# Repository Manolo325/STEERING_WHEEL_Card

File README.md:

# Volant
Mettre à jour la carte volant du TIM

# Fonctions à accomplir

- Programable de l'exterieur
- Affichage à l'écran de : 
	- La vitesse 
	- (Temoins freinage)
	- (Temoins feu avant /arrire)
	- (Temoins direction)

- Saisie de :
	- la vitesse limite
	- Phare avant / arriere
	- Feux de direction
	- Feu de freinage
	- Essuie glace 
	- marche avant/ marche arriere
	- acceleration
	- consigne de courant
	- POWER ON/OFF (potentiel)

- Communication CAN avec :
	- Lumiere avant/arriere
	- Feu de direction
	- Freinage (lumiere arriere)
	 ATTENTION : Cable signalant le freinage doit passer à coté du BUS CAN 
	- Vitesse 
	- Commande Moteur : Avant/Arriere/Courant

- ~~led temoins de :~~
	- ~~freinage~~
	- ~~feu de direction~~
	- ~~feu avant et arrire~~

# Materielle

- Affichache  :
	- (SPI) ecran e-paper hacked (refresh speed)
	- (SPI) ecran oled (potentiel ? )
- Saisie 
	- rotary encoder --> vitesse limite 
	- Potentiometre  --> selection consigne de courant 
	- lever switch   --> marche avant/arriere
	- push buttons   --> tous les autres

# limite mecanique (à chercher)

- le plus petit possible

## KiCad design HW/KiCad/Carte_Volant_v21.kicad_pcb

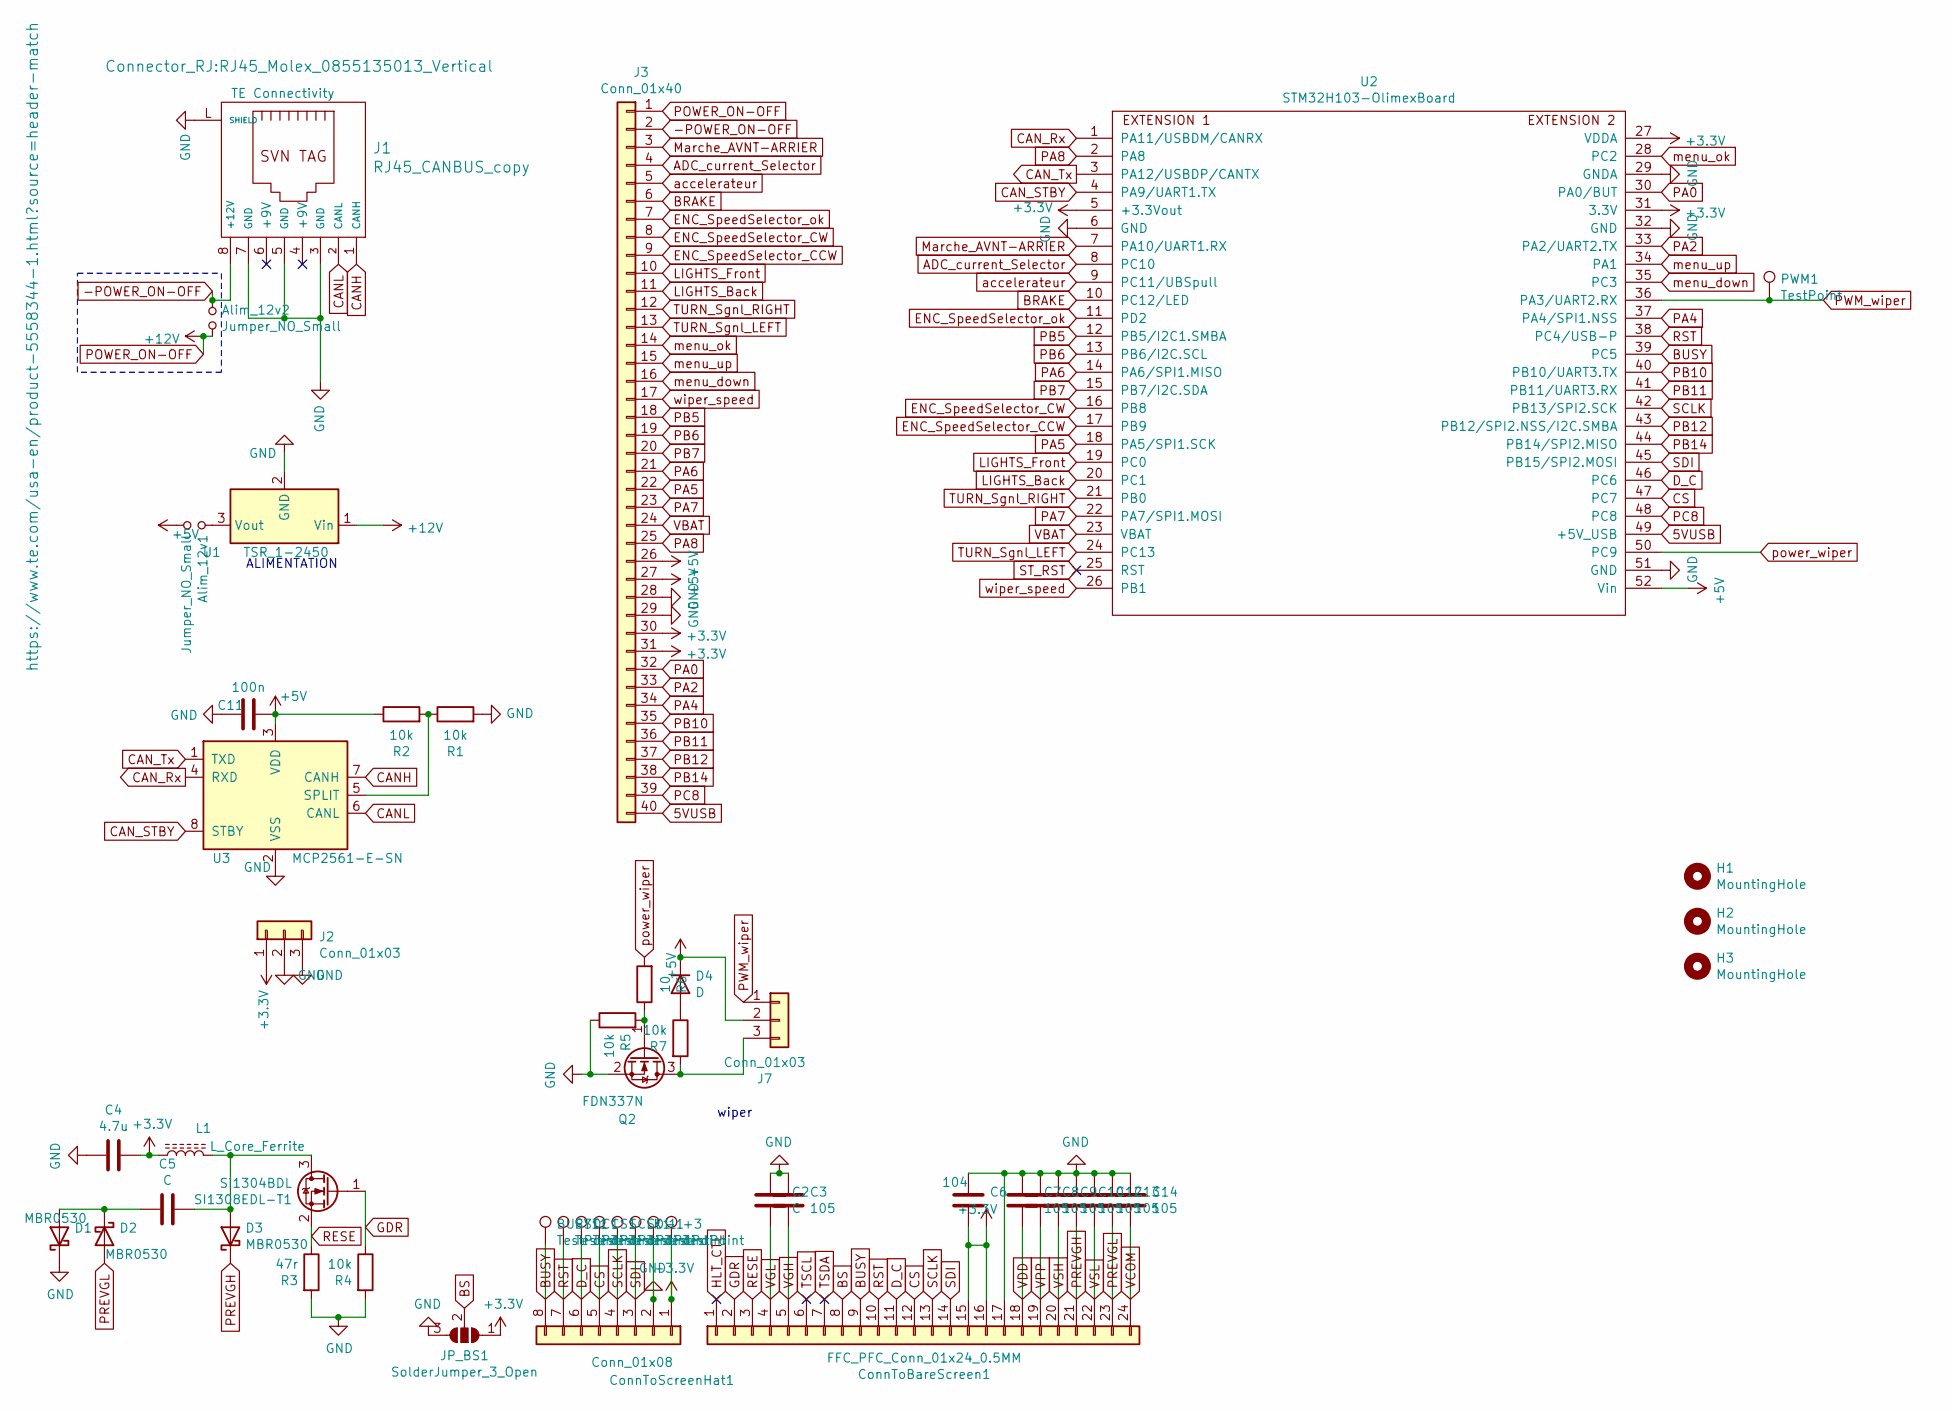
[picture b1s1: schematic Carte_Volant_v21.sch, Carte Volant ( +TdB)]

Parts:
+3: TestPoint; TestPoint_Pad_1.5x1.5mm
-1: TestPoint; TestPoint_Pad_1.5x1.5mm
Alim_12v1, Alim_12v2: Jumper_NO_Small; SolderJumper-2_P1.3mm_Open_Pad1.0x1.5mm
BUSY1: TestPoint; TestPoint_Pad_1.5x1.5mm
C2, C5: C; C_0603_1608Metric_Pad1.05x0.95mm_HandSolder
C3, C7, C8, C9, C10, C12, C13, C14: 105; C_0603_1608Metric_Pad1.05x0.95mm_HandSolder
C4: 4.7u; C_0603_1608Metric_Pad1.05x0.95mm_HandSolder
C6: 104; C_0603_1608Metric_Pad1.05x0.95mm_HandSolder
C11: 100n; C_0603_1608Metric_Pad1.05x0.95mm_HandSolder
CS1: TestPoint; TestPoint_Pad_1.5x1.5mm
ConnToBareScreen1: FFC_PFC_Conn_01x24_0.5MM; Hirose_FH12-24S-0.5SH_1x24-1MP_P0.50mm_Horizontal
ConnToScreenHat1: Conn_01x08; Molex_PicoBlade_53261-0871_1x08-1MP_P1.25mm_Horizontal
D1, D2, D3: MBR0530; D_SOD-123
D4: D; D_1206_3216Metric
DC1: TestPoint; TestPoint_Pad_1.5x1.5mm
H1, H2, H3: MountingHole; MountingHole_3.5mm
J1: RJ45_CANBUS_copy; RJ45_Molex_0855135013_Vertical; MPN 5558344-1
J2, J7: Conn_01x03; Molex_Micro-Fit_3.0_43650-0300_1x03_P3.00mm_Horizontal
J3: Conn_01x40; IDC-Header_2x20_P2.54mm_Vertical
JP_BS1: SolderJumper_3_Open; SolderJumper-3_P1.3mm_Open_Pad1.0x1.5mm
L1: L_Core_Ferrite; L_1206_3216Metric
PWM1: TestPoint; TestPoint_Pad_1.5x1.5mm
Q2: FDN337N; SOT-23
R1, R2, R4, R5, R7: 10k; R_0603_1608Metric_Pad1.05x0.95mm_HandSolder
R3: 47r; R_0603_1608Metric_Pad1.05x0.95mm_HandSolder
R6: 10; R_0603_1608Metric_Pad1.05x0.95mm_HandSolder
RST1: TestPoint; TestPoint_Pad_1.5x1.5mm
SCLK1: TestPoint; TestPoint_Pad_1.5x1.5mm
SDI1: TestPoint; TestPoint_Pad_1.5x1.5mm
SI1308EDL-T1: Si1304BDL; SOT-323_SC-70
U1: TSR_1-2450; Converter_DCDC_TRACO_TSR-1_THT
U2: STM32H103-OlimexBoard; STM32H103-Olimex_SMD
U3: MCP2561-E-SN; SOIC-8_3.9x4.9mm_P1.27mm

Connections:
5VUSB: J3.40, U2.49 (+5V_USB)
+3V3: +3.1, C4.1, C6.2, ConnToBareScreen1.15, ConnToBareScreen1.16, ConnToScreenHat1.1, J2.1, J3.30, J3.31, JP_BS1.1 (A), L1.1, U2.5 (+3.3Vout), U2.27 (VDDA), U2.31 (3.3V)
+5V: Alim_12v1.2, C11.2, D4.1 (K), J3.26, J3.27, J7.2, R2.1, U2.52 (Vin), U3.3 (VDD)
-POWER_ON-OFF: Alim_12v2.1, J1.8 (+12V), J3.2
ADC_current_Selector: J3.4, U2.8 (PC10)
BRAKE: J3.6, U2.10 (PC12/LED)
BS: ConnToBareScreen1.8, JP_BS1.2 (C)
BUSY: BUSY1.1, ConnToBareScreen1.9, ConnToScreenHat1.8, U2.39 (PC5)
CANH: J1.1 (CANH), U3.7 (CANH)
CANL: J1.2 (CANL), U3.6 (CANL)
CAN_Rx: U2.1 (PA11/USBDM/CANRX), U3.4 (RXD)
CAN_STBY: U2.4 (PA9/UART1.TX), U3.8 (STBY)
CAN_Tx: U2.3 (PA12/USBDP/CANTX), U3.1 (TXD)
CS: CS1.1, ConnToBareScreen1.12, ConnToScreenHat1.5, U2.47 (PC7)
D_C: ConnToBareScreen1.11, ConnToScreenHat1.6, DC1.1, U2.46 (PC6)
ENC_SpeedSelector_CCW: J3.9, U2.17 (PB9)
ENC_SpeedSelector_CW: J3.8, U2.16 (PB8)
ENC_SpeedSelector_ok: J3.7, U2.11 (PD2)
GDR: ConnToBareScreen1.2, R4.1, SI1308EDL-T1.1 (G)
GND: -1.1, C2.1, C3.1, C4.2, C6.1, C7.1, C8.1, C9.1, C10.1, C11.1, C12.1, C13.1, C14.1, ConnToBareScreen1.17, ConnToBareScreen1.MP, ConnToScreenHat1.2, ConnToScreenHat1.MP, D1.1 (K), J1.3 (GND), J1.5 (GND), J1.7 (GND), J1.L (SHIELD), J2.2, J2.3, J3.28, J3.29, JP_BS1.3 (B), Q2.2 (S), R1.2, R3.2, R4.2, R5.1, U1.2 (GND), U2.6 (GND), U2.29 (GNDA), U2.32 (GND), U2.51 (GND), U3.2 (VSS)
HLT_CTL: ConnToBareScreen1.1
LIGHTS_Back: J3.11, U2.20 (PC1)
LIGHTS_Front: J3.10, U2.19 (PC0)
Marche_AVNT-ARRIER: J3.3, U2.7 (PA10/UART1.RX)
unnamed: Alim_12v1.1, U1.3 (Vout)
unnamed: C5.1, D3.2 (A), L1.2, SI1308EDL-T1.3 (D)
unnamed: C5.2, D1.2 (A), D2.1 (K)
unnamed: D4.2 (A), R7.1
unnamed: J7.3, Q2.3 (D), R7.2
unnamed: Q2.1 (G), R5.2, R6.1
unnamed: R1.1, R2.2, U3.5 (SPLIT)
PA0: J3.32, U2.30 (PA0/BUT)
PA2: J3.33, U2.33 (PA2/UART2.TX)
PA4: J3.34, U2.37 (PA4/SPI1.NSS)
PA5: J3.22, U2.18 (PA5/SPI1.SCK)
PA6: J3.21, U2.14 (PA6/SPI1.MISO)
PA7: J3.23, U2.22 (PA7/SPI1.MOSI)
PA8: J3.25, U2.2 (PA8)
PB5: J3.18, U2.12 (PB5/I2C1.SMBA)
PB6: J3.19, U2.13 (PB6/I2C.SCL)
PB7: J3.20, U2.15 (PB7/I2C.SDA)
PB10: J3.35, U2.40 (PB10/UART3.TX)
PB11: J3.36, U2.41 (PB11/UART3.RX)
PB12: J3.37, U2.43 (PB12/SPI2.NSS/I2C.SMBA)
PB14: J3.38, U2.44 (PB14/SPI2.MISO)
PC8: J3.39, U2.48 (PC8)
POWER_ON-OFF: Alim_12v2.2, J3.1, U1.1 (Vin)
PREVGH: C10.2, ConnToBareScreen1.21, D3.1 (K)
PREVGL: C13.2, ConnToBareScreen1.23, D2.2 (A)
PWM_wiper: J7.1, PWM1.1, U2.36 (PA3/UART2.RX)
RESE: ConnToBareScreen1.3, R3.1, SI1308EDL-T1.2 (S)
RST: ConnToBareScreen1.10, ConnToScreenHat1.7, RST1.1, U2.38 (PC4/USB-P)
SCLK: ConnToBareScreen1.13, ConnToScreenHat1.4, SCLK1.1, U2.42 (PB13/SPI2.SCK)
SDI: ConnToBareScreen1.14, ConnToScreenHat1.3, SDI1.1, U2.45 (PB15/SPI2.MOSI)
ST_RST: U2.25 (RST)
TSCL: ConnToBareScreen1.6
TSDA: ConnToBareScreen1.7
TURN_Sgnl_LEFT: J3.13, U2.24 (PC13)
TURN_Sgnl_RIGHT: J3.12, U2.21 (PB0)
VBAT: J3.24, U2.23 (VBAT)
VCOM: C14.2, ConnToBareScreen1.24
VDD: C7.2, ConnToBareScreen1.18
VGH: C3.2, ConnToBareScreen1.5
VGL: C2.2, ConnToBareScreen1.4
VPP: C8.2, ConnToBareScreen1.19
VSH: C9.2, ConnToBareScreen1.20
VSL: C12.2, ConnToBareScreen1.22
accelerateur: J3.5, U2.9 (PC11/UBSpull)
menu_down: J3.16, U2.35 (PC3)
menu_ok: J3.14, U2.28 (PC2)
menu_up: J3.15, U2.34 (PA1)
power_wiper: R6.2, U2.50 (PC9)
wiper_speed: J3.17, U2.26 (PB1)

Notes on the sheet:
wiper
ALIMENTATION

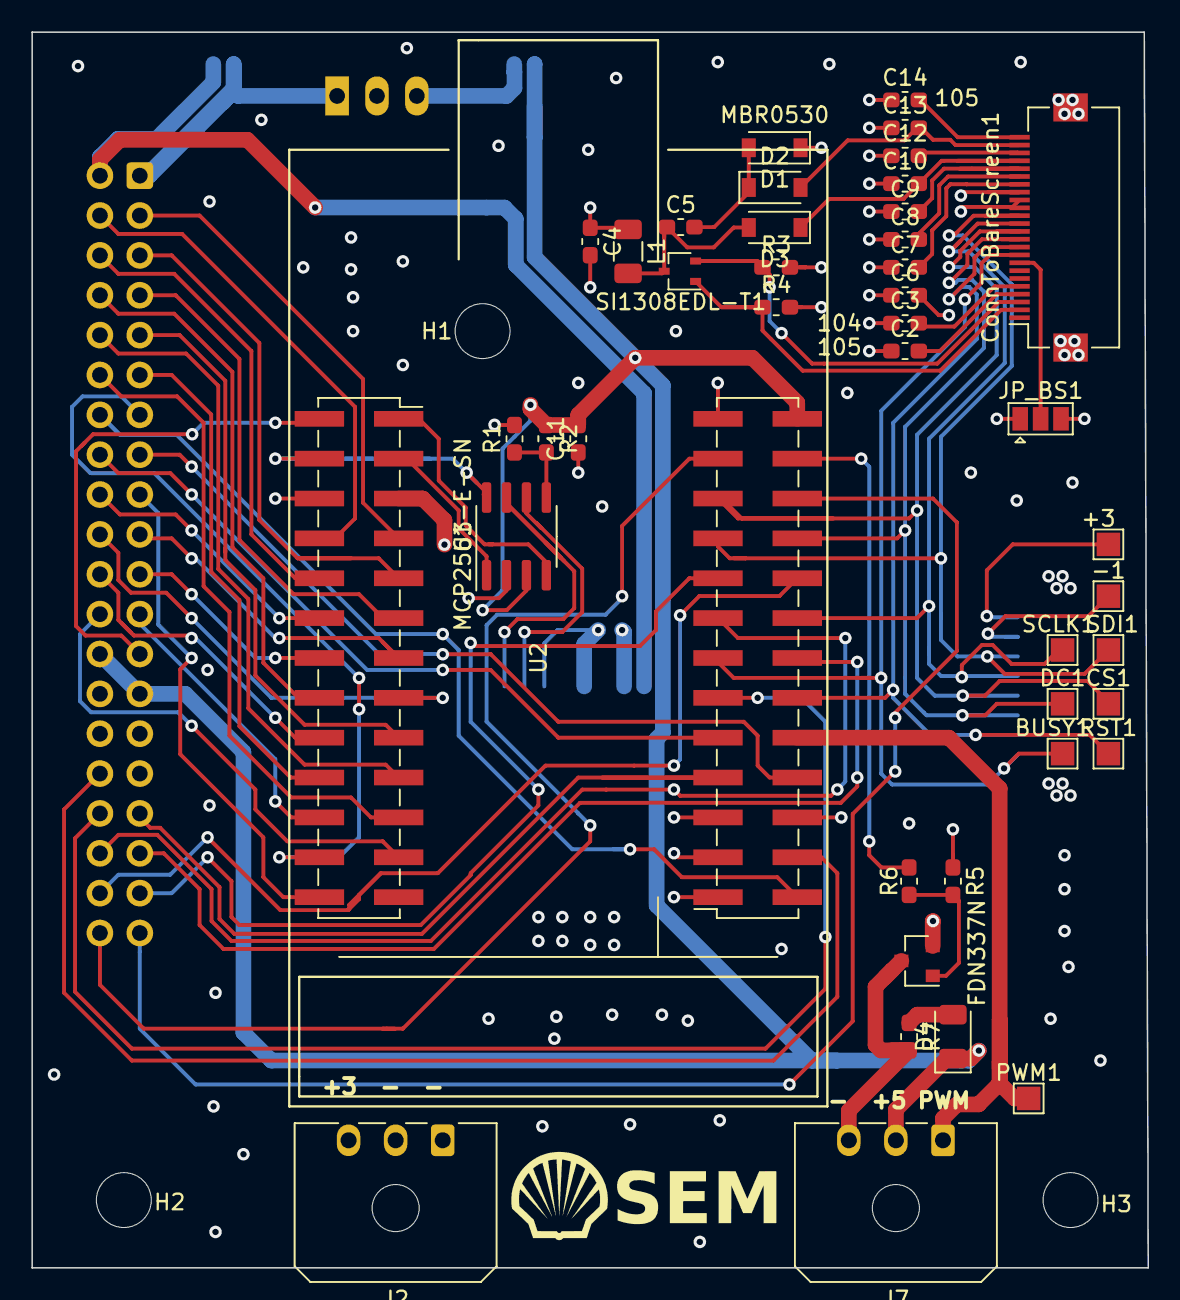
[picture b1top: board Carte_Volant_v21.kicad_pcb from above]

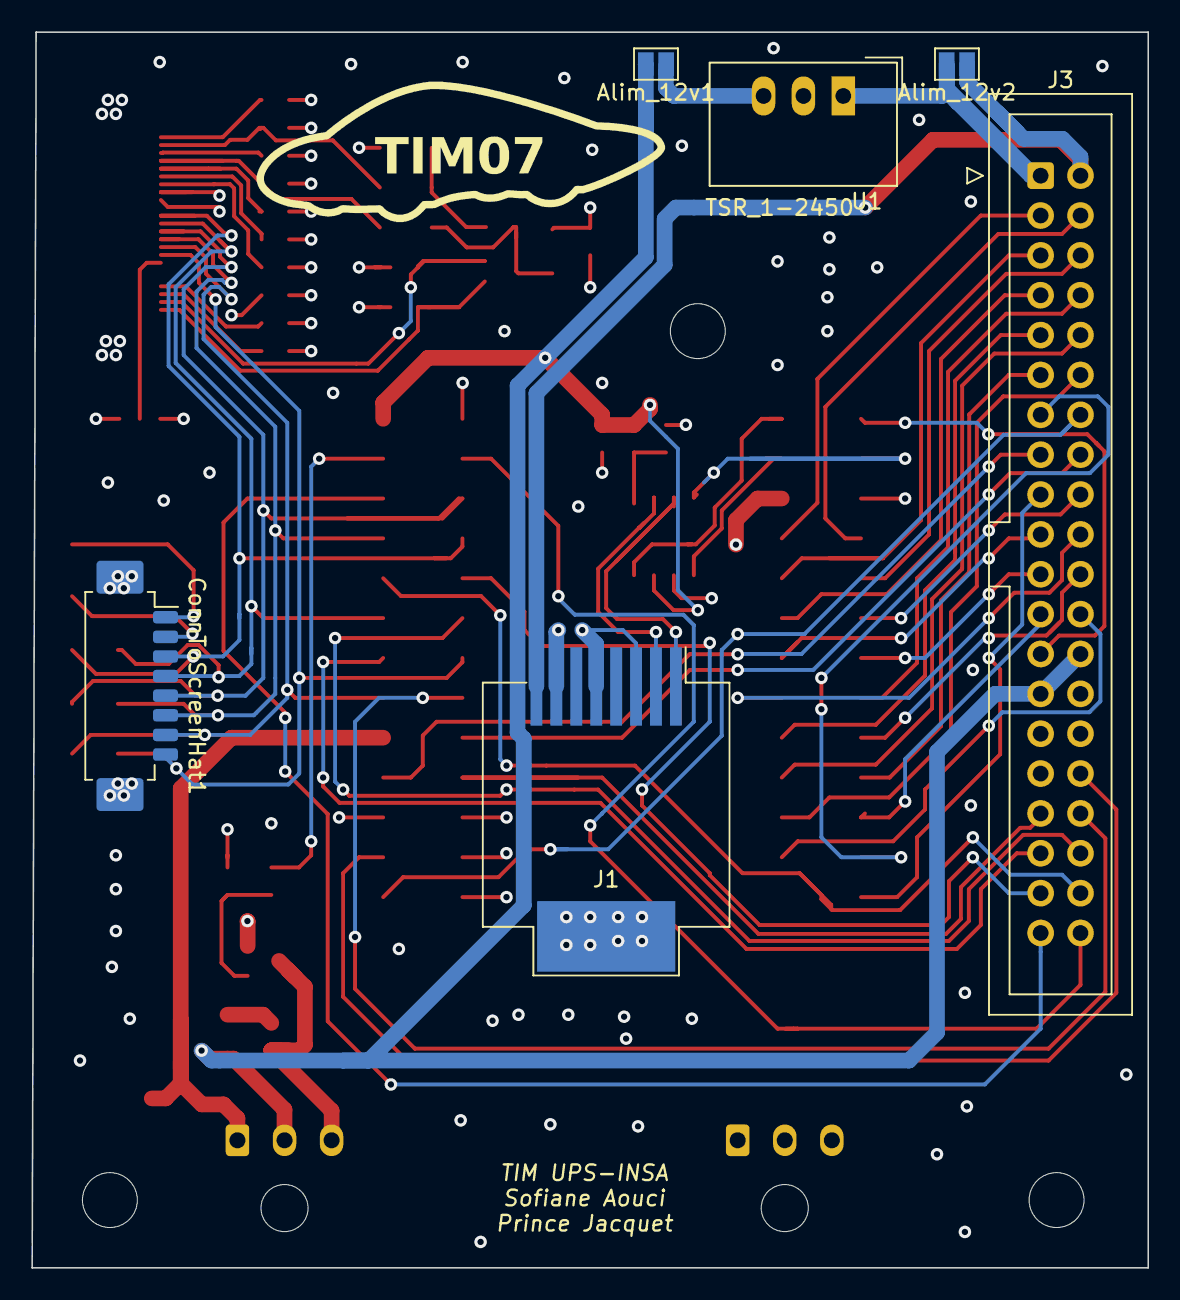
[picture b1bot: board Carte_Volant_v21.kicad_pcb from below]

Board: 4 copper layers, 71.1 x 78.7 mm, 53 parts (7 on the bottom side), 69 nets.

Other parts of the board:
VAL: REF; logo_tim07_medium_bottom
VAL#2: REF; logo_shell2_medium_top_silk

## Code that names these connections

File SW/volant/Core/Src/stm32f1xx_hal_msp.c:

/* USER CODE BEGIN Header */
/**
  ******************************************************************************
  * File Name          : stm32f1xx_hal_msp.c
  * Description        : This file provides code for the MSP Initialization
  *                      and de-Initialization codes.
  ******************************************************************************
  * @attention
  *
  * <h2><center>&copy; Copyright (c) 2020 STMicroelectronics.
  * All rights reserved.</center></h2>
  *
  * This software component is licensed by ST under BSD 3-Clause license,
  * the "License"; You may not use this file except in compliance with the
  * License. You may obtain a copy of the License at:
  *                        opensource.org/licenses/BSD-3-Clause
  *
  ******************************************************************************
  */
/* USER CODE END Header */

/* Includes ------------------------------------------------------------------*/
#include "main.h"
/* USER CODE BEGIN Includes */

/* USER CODE END Includes */

/* Private typedef -----------------------------------------------------------*/
/* USER CODE BEGIN TD */

/* USER CODE END TD */

/* Private define ------------------------------------------------------------*/
/* USER CODE BEGIN Define */

/* USER CODE END Define */

/* Private macro -------------------------------------------------------------*/
/* USER CODE BEGIN Macro */

/* USER CODE END Macro */

/* Private variables ---------------------------------------------------------*/
/* USER CODE BEGIN PV */

/* USER CODE END PV */

/* Private function prototypes -----------------------------------------------*/
/* USER CODE BEGIN PFP */

/* USER CODE END PFP */

/* External functions --------------------------------------------------------*/
/* USER CODE BEGIN ExternalFunctions */

/* USER CODE END ExternalFunctions */

/* USER CODE BEGIN 0 */

/* USER CODE END 0 */
/**
  * Initializes the Global MSP.
  */
void HAL_MspInit(void)
{
  /* USER CODE BEGIN MspInit 0 */

  /* USER CODE END MspInit 0 */

  __HAL_RCC_AFIO_CLK_ENABLE();
  __HAL_RCC_PWR_CLK_ENABLE();

  /* System interrupt init*/

  /** DISABLE: JTAG-DP Disabled and SW-DP Disabled
  */
  __HAL_AFIO_REMAP_SWJ_DISABLE();

  /* USER CODE BEGIN MspInit 1 */

  /* USER CODE END MspInit 1 */
}

/**
* @brief CAN MSP Initialization
* This function configures the hardware resources used in this example
* @param hcan: CAN handle pointer
* @retval None
*/
void HAL_CAN_MspInit(CAN_HandleTypeDef* hcan)
{
  GPIO_InitTypeDef GPIO_InitStruct = {0};
  if(hcan->Instance==CAN1)
  {
  /* USER CODE BEGIN CAN1_MspInit 0 */

  /* USER CODE END CAN1_MspInit 0 */
    /* Peripheral clock enable */
    __HAL_RCC_CAN1_CLK_ENABLE();

    __HAL_RCC_GPIOA_CLK_ENABLE();
    /**CAN GPIO Configuration
    PA11     ------> CAN_RX
    PA12     ------> CAN_TX
    */
    GPIO_InitStruct.Pin = GPIO_PIN_11;
    GPIO_InitStruct.Mode = GPIO_MODE_INPUT;
    GPIO_InitStruct.Pull = GPIO_NOPULL;
    HAL_GPIO_Init(GPIOA, &GPIO_InitStruct);

    GPIO_InitStruct.Pin = GPIO_PIN_12;
    GPIO_InitStruct.Mode = GPIO_MODE_AF_PP;
    GPIO_InitStruct.Speed = GPIO_SPEED_FREQ_HIGH;
    HAL_GPIO_Init(GPIOA, &GPIO_InitStruct);

  /* USER CODE BEGIN CAN1_MspInit 1 */

  /* USER CODE END CAN1_MspInit 1 */
  }

}

/**
* @brief CAN MSP De-Initialization
* This function freeze the hardware resources used in this example
* @param hcan: CAN handle pointer
* @retval None
*/
void HAL_CAN_MspDeInit(CAN_HandleTypeDef* hcan)
{
  if(hcan->Instance==CAN1)
  {
  /* USER CODE BEGIN CAN1_MspDeInit 0 */

  /* USER CODE END CAN1_MspDeInit 0 */
    /* Peripheral clock disable */
    __HAL_RCC_CAN1_CLK_DISABLE();

    /**CAN GPIO Configuration
    PA11     ------> CAN_RX
    PA12     ------> CAN_TX
    */
    HAL_GPIO_DeInit(GPIOA, GPIO_PIN_11|GPIO_PIN_12);

  /* USER CODE BEGIN CAN1_MspDeInit 1 */

  /* USER CODE END CAN1_MspDeInit 1 */
  }

}

/**
* @brief SPI MSP Initialization
* This function configures the hardware resources used in this example
* @param hspi: SPI handle pointer
* @retval None
*/
void HAL_SPI_MspInit(SPI_HandleTypeDef* hspi)
{
  GPIO_InitTypeDef GPIO_InitStruct = {0};
  if(hspi->Instance==SPI2)
  {
  /* USER CODE BEGIN SPI2_MspInit 0 */

  /* USER CODE END SPI2_MspInit 0 */
    /* Peripheral clock enable */
    __HAL_RCC_SPI2_CLK_ENABLE();

    __HAL_RCC_GPIOB_CLK_ENABLE();
    /**SPI2 GPIO Configuration
    PB13     ------> SPI2_SCK
    PB14     ------> SPI2_MISO
    PB15     ------> SPI2_MOSI
    */
    GPIO_InitStruct.Pin = GPIO_PIN_13|GPIO_PIN_15;
    GPIO_InitStruct.Mode = GPIO_MODE_AF_PP;
    GPIO_InitStruct.Speed = GPIO_SPEED_FREQ_HIGH;
    HAL_GPIO_Init(GPIOB, &GPIO_InitStruct);

    GPIO_InitStruct.Pin = GPIO_PIN_14;
    GPIO_InitStruct.Mode = GPIO_MODE_INPUT;
    GPIO_InitStruct.Pull = GPIO_NOPULL;
    HAL_GPIO_Init(GPIOB, &GPIO_InitStruct);

  /* USER CODE BEGIN SPI2_MspInit 1 */

  /* USER CODE END SPI2_MspInit 1 */
  }

}

/**
* @brief SPI MSP De-Initialization
* This function freeze the hardware resources used in this example
* @param hspi: SPI handle pointer
* @retval None
*/
void HAL_SPI_MspDeInit(SPI_HandleTypeDef* hspi)
{
  if(hspi->Instance==SPI2)
  {
  /* USER CODE BEGIN SPI2_MspDeInit 0 */

  /* USER CODE END SPI2_MspDeInit 0 */
    /* Peripheral clock disable */
    __HAL_RCC_SPI2_CLK_DISABLE();

    /**SPI2 GPIO Configuration
    PB13     ------> SPI2_SCK
    PB14     ------> SPI2_MISO
    PB15     ------> SPI2_MOSI
    */
    HAL_GPIO_DeInit(GPIOB, GPIO_PIN_13|GPIO_PIN_14|GPIO_PIN_15);

  /* USER CODE BEGIN SPI2_MspDeInit 1 */

  /* USER CODE END SPI2_MspDeInit 1 */
  }

}

/* USER CODE BEGIN 1 */

/* USER CODE END 1 */

/************************ (C) COPYRIGHT STMicroelectronics *****END OF FILE****/

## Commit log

2019-09-20 Schéma Fonctionnel
2019-09-21 Added SchémaFonctionel_CarteVolant.drawio
2019-09-21 draft 1- SchémaFonctionel_CarteVolant.drawio
2019-09-21 Légende ajouter
2020-07-30 cahier des charges V.0
2020-07-30 beta cahier des charges
2020-10-24 V2.1
    - reversed Ethernet footprint
    - reversed text 3v gnd gnd
2020-10-24 removed files mentioned in KiCad.gitignore
2020-10-24 SW Initialization
2020-10-24 generate .c/.h
